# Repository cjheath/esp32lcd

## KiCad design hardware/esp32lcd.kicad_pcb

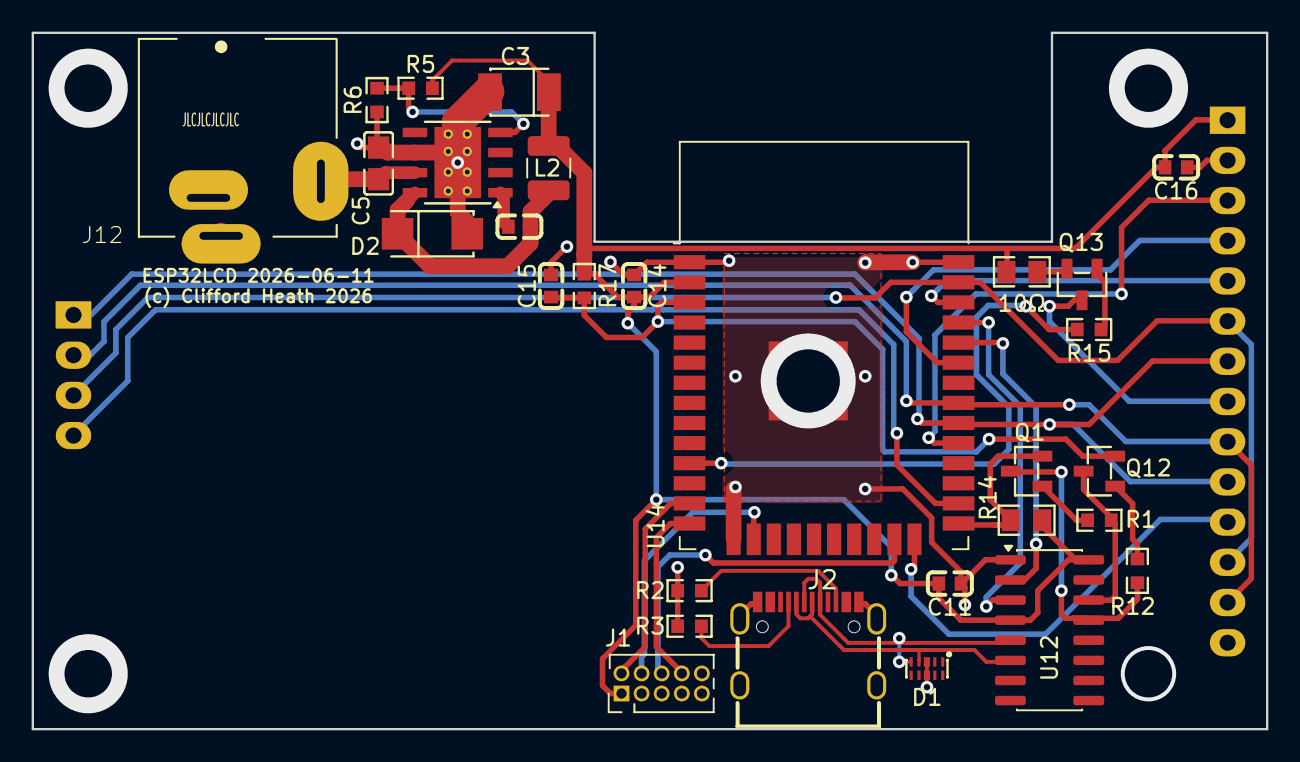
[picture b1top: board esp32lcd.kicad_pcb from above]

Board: 2 copper layers, 78.0 x 44.0 mm, 30 parts (1 on the bottom side), 34 nets.

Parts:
C3: 100uF; CASE-B_3528
C4: 10nF; C0603
C5: 4.7uF; C0805
C11, C14, C15, C16: 100nF; C0603
D1: TPAZ1143-04F; DFN-10_L2.5-W1.0-P0.50-BL-A
D2: SS34; SMA_L4.3-W2.6-LS5.2-RD
J1: Conn_02x05_Odd_Even; PinHeader_2x05_P1.27mm_Vertical
J2: USB_C_Receptacle_USB2.0_14P; USB-C_SMD-TYPE-C-31-M-12
J12: Barrel_Jack_Switch; XKB-DC-009A-2.0
L2: 15µH; L_1210_3225Metric
Q1, Q12: MMBT2222A; SOT-23-3_L2.9-W1.3-P1.90-LS2.4-BR
Q13: MMBT5401; SOT-23-3_L2.9-W1.3-P1.90-LS2.4-BR
R1, R5, R12, R17: 10kΩ; R0603
R2, R3: 5.1kΩ; R0603
R6: 5.6kΩ; R0603
R14: 100kΩ; R0805
R15: 220Ω; R0603
R16: 10Ω; R0805_NEW
U3: TPS5430; TI_SO-PowerPAD-8_ThermalVias
U12: CH340C; SOIC-16_3.9x9.9mm_P1.27mm
U14: ESP32-WROOM-32D; ESP32-WROOM-32
U15: ILI9341_SPI_Touch_SD; TJCTM24024-SPI

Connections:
+3V3: C3.1, C11.2, C14.2, C16.2, J1.1, L2.2, R5.2, R14.2, R16.1, R17.1, U12.4 (V3), U12.16 (VCC), U14.2 (VDD), U15.1 (VCC)
+SUPPLY: C5.2, J12.2, U3.7 (VIN)
/D+: D1.5 (I/O_4), J2.A6 (D+), J2.B6 (D+), U12.5 (UD+)
/D-: D1.4 (I/O_3), J2.A7 (D-), J2.B7 (D-), U12.6 (UD-)
BACKLIGHT: R15.2, U14.11 (IO26)
ESP_EN: C15.2, Q12.2 (C), R17.2, U14.3 (EN)
GND: C3.2, C5.1, C11.1, C14.1, C15.1, C16.1, D1.3 (GND), D1.8 (GND), D2.2 (A), J1.3, J1.5, J1.7, J1.9, J2.A1 (GND), J2.A12 (GND), J2.SH (SHIELD), J12.1, R2.1, R3.1, R6.1, U3.6 (GND), U3.9 (GNDPAD), U12.1 (GND), U14.1 (GND), U14.15 (GND), U14.38 (GND), U14.39 (GND), U15.2 (GND)
LCDDC: U14.36 (IO22), U15.5 (D/C)
LCDLED: Q13.3 (C), U15.8 (LED)
LCDRST: U14.33 (IO21), U15.4 (RESET)
LOAD: Q1.2 (C), R14.1, U14.25 (IO0)
unnamed: C4.2, D2.1 (K), L2.1, U3.8 (PH)
unnamed: J1.2, U14.13 (IO14)
unnamed: J1.4, U14.16 (IO13)
unnamed: J1.6, U14.23 (IO15)
unnamed: J1.8, U14.14 (IO12)
unnamed: J2.A5 (CC1), R3.2
unnamed: J2.B5 (CC2), R2.2
unnamed: Q1.1 (B), R1.1
unnamed: Q1.3 (E), R12.2, U12.13 (~DTR)
unnamed: Q12.1 (B), R12.1
unnamed: Q12.3 (E), R1.2, U12.14 (~RTS)
unnamed: Q13.1 (B), R15.1
unnamed: Q13.2 (E), R16.2
unnamed: C4.1, U3.1 (BOOT)
unnamed: R5.1, R6.2, U3.4 (VSENSE)
RXD0: U12.2 (TXD), U14.34 (RXD0/IO3)
TXD0: U12.3 (RXD), U14.35 (TXD0/IO1)
VSPICLK: U14.30 (IO18), U15.7 (SCK), U15.10 (T_CLK), U15.15 (SD_SCK)
VSPICS0: U14.29 (IO5), U15.3 (CS)
VSPICS1: U14.26 (IO4), U15.18 (SD_CS)
VSPICS2: U14.24 (IO2), U15.11 (T_CS)
VSPIDATA: U14.37 (IO23), U15.6 (MOSI), U15.12 (T_DIN), U15.17 (SD_MOSI)
VSPIDIN: U14.31 (IO19), U15.9 (MISO), U15.13 (T_DO), U15.16 (SD_MISO)

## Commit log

2021-01-11 First version esp32lcd
2021-01-11 Added initial fabrication files
2021-01-11 Added .gitignore
2021-01-11 Switched TxD and RxD between the two chips
2021-01-12 Ditched diode steering in favour of another transistor
2021-05-04 Deleted GPIO2 boot pulldown
2021-09-25 Updated to add JTAG debug
2021-09-26 Moved hardware design into a subdirectory
2026-06-12 Last version before moving to Kicad10 and JLC Basic/Extended libraries
2026-06-12 Moved to Kicad 10 and JLC Basic/Extended parts where possible
